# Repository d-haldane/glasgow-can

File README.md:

# Glasgow CAN Interface Addon

This repository provides the hardware and software components of a CAN Interface Addon for the [Glasgow Digital Interface Explorer](https://github.com/GlasgowEmbedded/glasgow).

A rough spec is outlined below:

- Sits directly on top of a Glasgow board
- 2x CAN interfaces, available on port A and B respectively
- Standard DE-9 connectors, suitable for use with OBD-II cables
- Isolation between each CAN port and the Glasgow (and host)
- CAN FD support

This repository (will) contain both hardware and software components of this addon.
Out-of-Tree support will be required when work on the applet begins (see PR [#213](https://github.com/GlasgowEmbedded/glasgow/pull/213)).

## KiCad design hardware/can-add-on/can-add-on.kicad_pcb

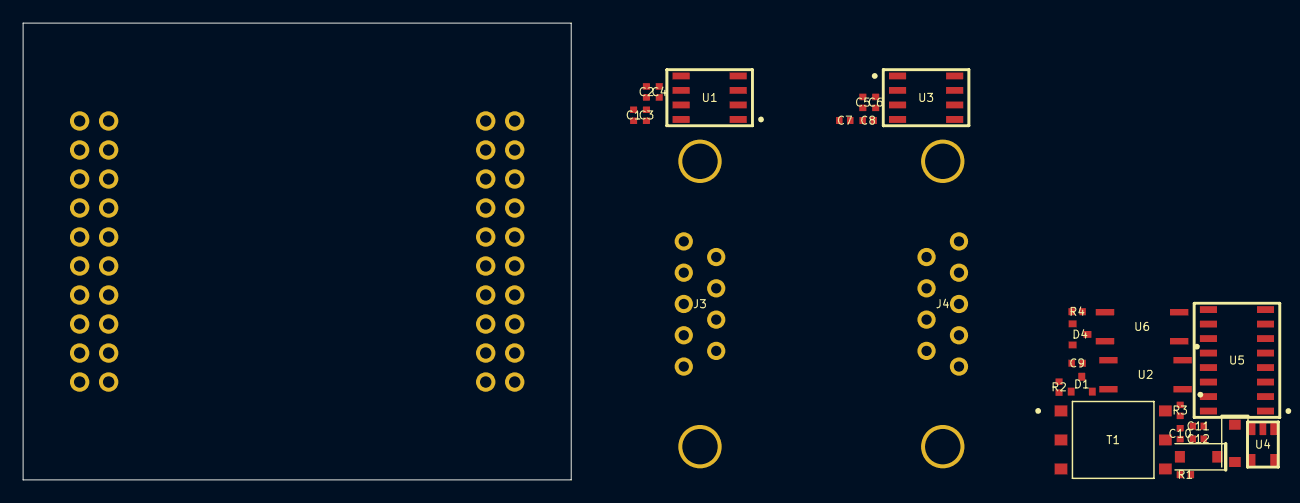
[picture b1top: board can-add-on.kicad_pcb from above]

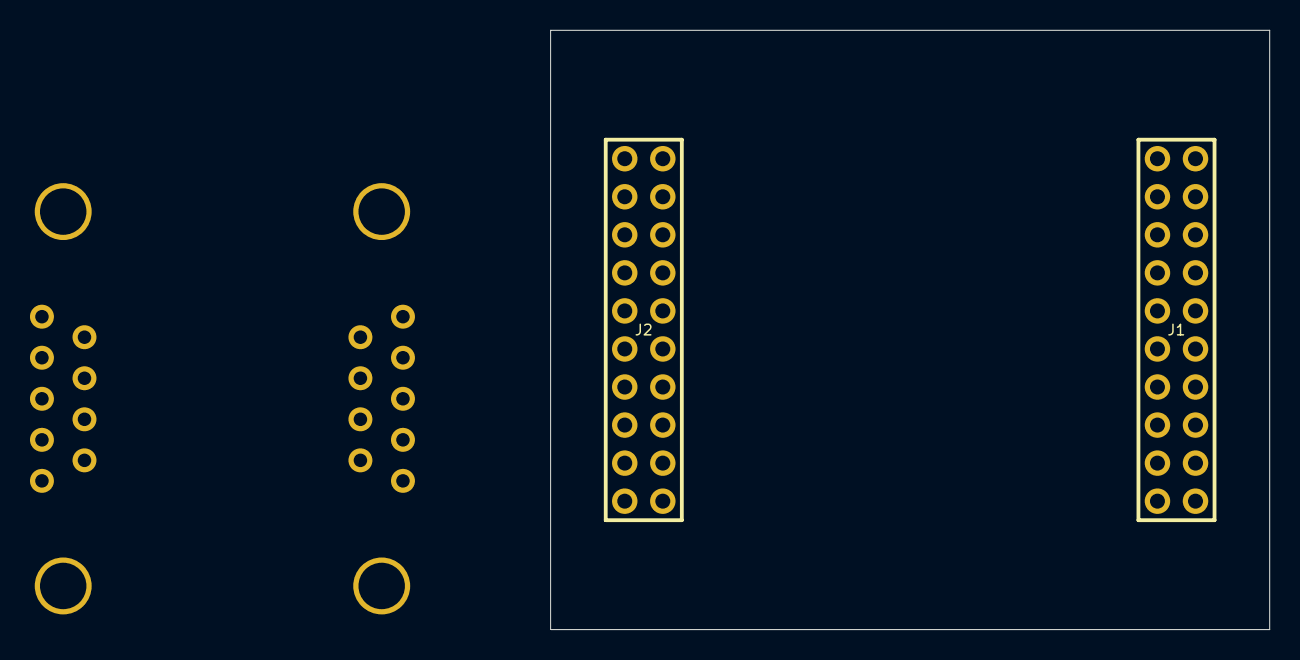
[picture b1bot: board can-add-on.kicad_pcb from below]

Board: 2 copper layers, 48.0 x 40.0 mm, 29 parts (2 on the bottom side), 26 nets, no tracks yet.

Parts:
C1, C2, C3, C4, C5, C6, C7, C8, C9, C10, C11, C12: ipc-two-pin-package$28
D1, D4: SC-70-3
J1, J2: pin-header-pkg$17
J3: amphenol-delta-d-pkg$36
J4: amphenol-delta-d-pkg$50
R1, R2, R3, R4: ipc-two-pin-package$28
T1: xfmr-760390012
U1, U3: soic127p-package$23
U2, U6: tlp-175
U4: SOT95P280X145-5N
U5: soic127p-package$65

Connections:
CANA-H: D1.1, J3.3, R2.1, U1.7
CANA-L: D1.2, J3.5, U1.6, U2.6
CANA-RX: J1.6, U1.4
CANA-S: J1.8, U1.8
CANA-TX: J1.4, U1.1
ISO-GND: C5.2, C6.2, C7.2, C8.2, C10.2, C12.2, D4.3, J4.2, J4.10, J4.11, T1.5, U3.2, U5.9, U5.15
VIO-A: C1.1, C2.1, C3.1, C4.1, J2.1, U1.3, U1.5
VIO-B: C9.1, C11.1, J1.1, T1.2, U4.2, U5.1, U5.7
VIO-B-ISO: C5.1, C6.1, C7.1, C8.1, C10.1, C12.1, U3.3, U3.5, U5.10, U5.16
glasgow_PA4: J1.10, R1.1
glasgow_PB1: J2.3, U5.3
glasgow_PB2: J2.5, U5.6
glasgow_PB3: J2.7, U5.4
glasgow_PB4: J2.9, R3.1
gnd: C1.2, C2.2, C3.2, C4.2, C9.2, C11.2, D1.3, J1.3, J1.5, J1.7, J1.9, J1.11, J1.13, J1.15, J1.17, J2.4, J2.6, J2.8, J2.10, J2.12, J2.14, J2.16, J2.18, J3.2, J3.10, J3.11, U1.2, U2.3, U4.4, U4.5, U5.2, U5.8, U6.3
net_iso$51_xfrmr_p1: T1.1, U4.3
net_iso$51_xfrmr_p3: T1.3, U4.1
net_j-b_p5: D4.2, J4.5, U3.6, U6.6
net_rid$47_p2: R2.2, U2.4
net_rid$71_p1: D4.1, J4.3, R4.1, U3.7
net_rid$71_p2: R4.2, U6.4
net_ssr$42_a: R1.2, U2.1
net_ssr$69_a: R3.2, U6.1
net_xr-b_s: U3.8, U5.13
net_xr-b_uart_rx: U3.4, U5.11
net_xr-b_uart_tx: U3.1, U5.14

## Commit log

2020-10-16 initial outline / spec
2020-10-16 Add design generator, set up glasgow
2020-10-16 Add stuff to ocdb, include a can tran
2020-10-17 Add ESD clamps
2020-10-17 Add generated kicad project
2020-10-20 Factor out glasgow
2020-10-22 REfactor glasgow model
2020-10-22 Update generated kicad
2020-10-22 Update gnd connections for isolation
2020-10-22 Update ocdb to fix fet symbols
2020-11-18 Regenerate kicad with power/gnd symbols
